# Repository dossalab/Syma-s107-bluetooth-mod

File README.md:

## Syma S107 Bluetooth mod

Syma S107 is a toy helicopter model being popular in early-2010s. It's rather well known because of its low cost, good flying characteristics and sturdy body resistant to crashes.

The original remote control system uses infrared communication - similar to how classic TV remotes work. The major drawback of such solution is that it's very sensitive to direct sunlight - making it very hard (and even slightly dangerous) to fly this toy outside. This also requires keeping a dedicated remote which is larger than this toy and always tend to go missing :)

This is a complete redesign of original motherboard, featuring Bluetooth LE with broader range and smartphone compatibility, battery charger with USB port and battery level reporting, additional outputs and custom, hackable firmware!

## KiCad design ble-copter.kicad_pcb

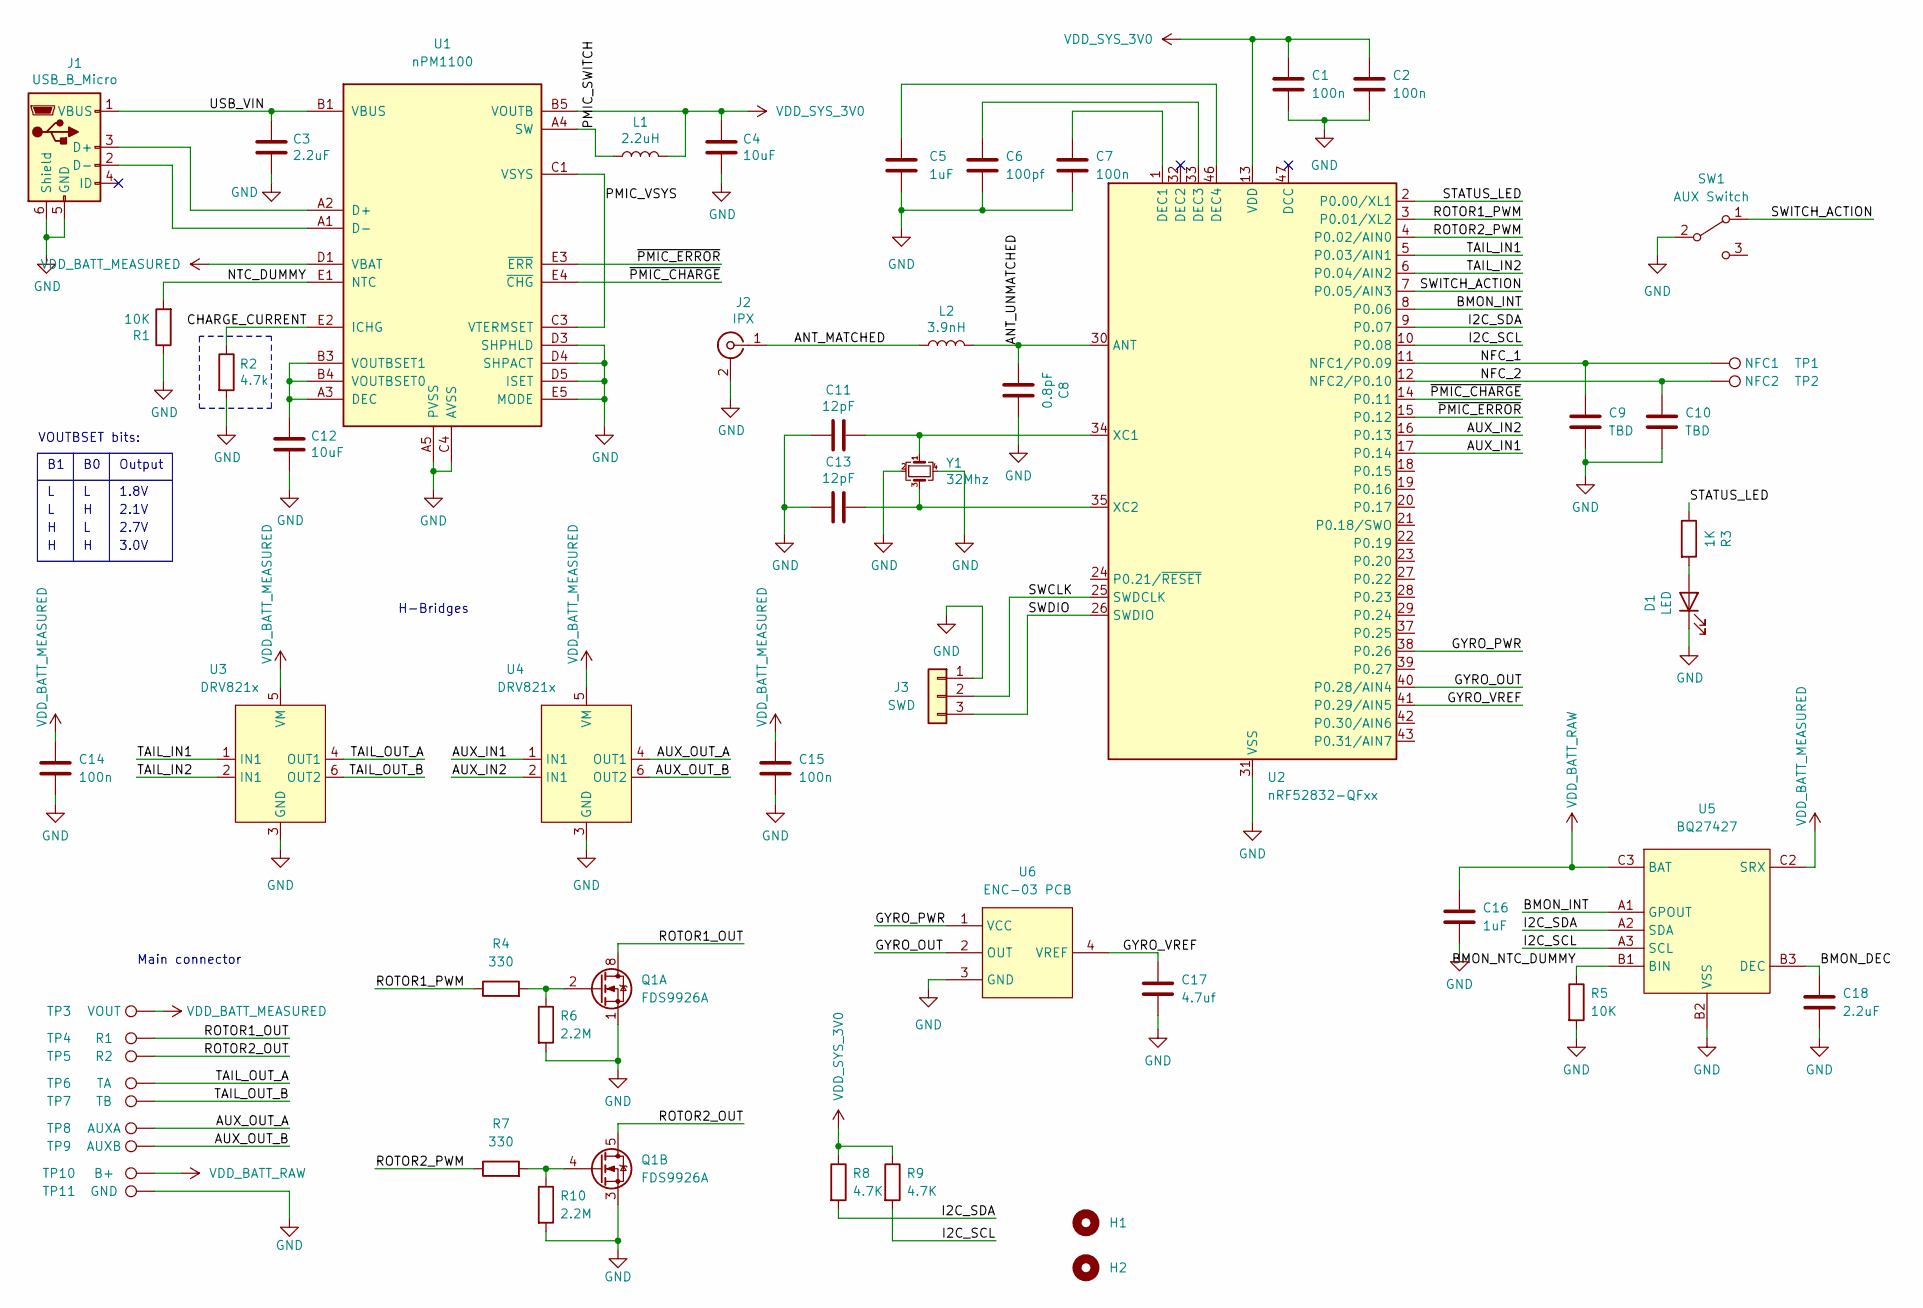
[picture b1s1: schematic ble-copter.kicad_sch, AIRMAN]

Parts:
C1, C2, C7, C14, C15: 100n; C_0603_1608Metric
C3, C18: 2.2uF; C_0603_1608Metric
C4, C12: 10uF; C_0603_1608Metric
C5, C16: 1uF; C_0603_1608Metric
C6: 100pf; C_0603_1608Metric
C8: 0.8pF; C_0603_1608Metric
C9, C10: TBD; C_0603_1608Metric
C11, C13: 12pF; C_0603_1608Metric
C17: 4.7uf; C_0603_1608Metric
D1: LED; LED_0603_1608Metric
H1, H2: MountingHole; MountingHole_1.6mm
J1: USB_B_Micro; USB_Micro-B_Wuerth_629105150521
J2: IPX; U.FL_Hirose_U.FL-R-SMT-1_Vertical
J3: SWD; PinHeader_1x03_P1.27mm_Vertical
L1: 2.2uH; L_0805_2012Metric
L2: 3.9nH; L_0603_1608Metric
Q1: FDS9926A; SOIC-8_3.9x4.9mm_P1.27mm
R1, R5: 10K; R_0603_1608Metric
R2: 4.7k; R_0603_1608Metric
R3: 1K; R_0603_1608Metric
R4, R7: 330; R_0603_1608Metric
R6, R10: 2.2M; R_0603_1608Metric
R8, R9: 4.7K; R_0603_1608Metric
SW1: AUX Switch; SW_SPDT_PCM12
TP1: NFC1; TestPoint_THTPad_D1.0mm_Drill0.5mm
TP2: NFC2; TestPoint_THTPad_D1.0mm_Drill0.5mm
TP3: VOUT; TestPoint_THTPad_D1.0mm_Drill0.5mm
TP4: R1; TestPoint_THTPad_D1.0mm_Drill0.5mm
TP5: R2; TestPoint_THTPad_D1.0mm_Drill0.5mm
TP6: TA; TestPoint_THTPad_D1.0mm_Drill0.5mm
TP7: TB; TestPoint_THTPad_D1.0mm_Drill0.5mm
TP8: AUXA; TestPoint_THTPad_D1.0mm_Drill0.5mm
TP9: AUXB; TestPoint_THTPad_D1.0mm_Drill0.5mm
TP10: B+; TestPoint_THTPad_D1.0mm_Drill0.5mm
TP11: GND; TestPoint_THTPad_D1.0mm_Drill0.5mm
U1: nPM1100; Nordic_WLCSP-25_5x5_2.075x2.075mm
U2: nRF52832-QFxx; QFN-48-1EP_6x6mm_P0.4mm_EP4.6x4.6mm
U3, U4: DRV821x; SOT-563
U5: BQ27427; BGA-9_3x3_1.6x1.6mm
U6: ENC-03 PCB
Y1: 32Mhz; Crystal_SMD_2520-4Pin_2.5x2.0mm

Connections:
/ANT_MATCHED: J2.1 (In), L2.1
/ANT_UNMATCHED: C8.2, L2.2, U2.30 (ANT)
/AUX_IN1: U2.17 (P0.14), U4.1 (IN1)
/AUX_IN2: U2.16 (P0.13), U4.2 (IN1)
/AUX_OUT_A: TP8.1, U4.4 (OUT1)
/AUX_OUT_B: TP9.1, U4.6 (OUT2)
/BMON_DEC: C18.1, U5.B3 (DEC)
/BMON_INT: U2.8 (P0.06), U5.A1 (GPOUT)
/BMON_NTC_DUMMY: R5.1, U5.B1 (BIN)
/CHARGE_CURRENT: R2.1, U1.E2 (ICHG)
/GYRO_OUT: U2.40 (P0.28/AIN4), U6.2 (OUT)
/GYRO_PWR: U2.38 (P0.26), U6.1 (VCC)
/GYRO_VREF: C17.1, U2.41 (P0.29/AIN5), U6.4 (VREF)
/I2C_SCL: R9.2, U2.10 (P0.08), U5.A3 (SCL)
/I2C_SDA: R8.2, U2.9 (P0.07), U5.A2 (SDA)
/NFC_1: C9.1, TP1.1, U2.11 (NFC1/P0.09)
/NFC_2: C10.1, TP2.1, U2.12 (NFC2/P0.10)
/NTC_DUMMY: R1.2, U1.E1 (NTC)
/PMIC_SWITCH: L1.1, U1.A4 (SW)
/PMIC_VSYS: U1.C1 (VSYS), U1.C2 (VSYS), U1.C3 (VTERMSET)
/ROTOR1_OUT: Q1.7 (D1), Q1.8 (D1), TP4.1
/ROTOR1_PWM: R4.1, U2.3 (P0.01/XL2)
/ROTOR2_OUT: Q1.5 (D2), Q1.6 (D2), TP5.1
/ROTOR2_PWM: R7.1, U2.4 (P0.02/AIN0)
/STATUS_LED: R3.1, U2.2 (P0.00/XL1)
/SWCLK: J3.2, U2.25 (SWDCLK)
/SWDIO: J3.3, U2.26 (SWDIO)
/SWITCH_ACTION: SW1.1 (A), U2.7 (P0.05/AIN3)
/TAIL_IN1: U2.5 (P0.03/AIN1), U3.1 (IN1)
/TAIL_IN2: U2.6 (P0.04/AIN2), U3.2 (IN1)
/TAIL_OUT_A: TP6.1, U3.4 (OUT1)
/TAIL_OUT_B: TP7.1, U3.6 (OUT2)
/~PMIC_CHARGE: U1.E4 (~CHG), U2.14 (P0.11)
/~PMIC_ERROR: U1.E3 (~ERR), U2.15 (P0.12)
GND: C1.2, C2.2, C3.2, C4.2, C5.2, C6.2, C7.2, C8.1, C9.2, C10.2, C11.2, C12.2, C13.2, C14.2, C15.2, C16.2, C17.2, C18.2, D1.1 (K), J1.5 (GND), J1.6 (Shield), J2.2 (Ext), J3.1, Q1.1 (S1), Q1.3 (S2), R1.1, R2.2, R5.2, R6.2, R10.2, SW1.2 (B), TP11.1, U1.A5 (PVSS), U1.C4 (AVSS), U1.C5 (AVSS), U1.D3 (SHPHLD), U1.D4 (SHPACT), U1.D5 (ISET), U1.E5 (MODE), U2.31 (VSS), U2.45 (VSS), U2.49 (VSS), U3.3 (GND), U4.3 (GND), U5.B2 (VSS), U5.C1 (VSS), U6.3 (GND), Y1.2, Y1.4
unnamed: C5.1, U2.46 (DEC4)
unnamed: C6.1, U2.33 (DEC3)
unnamed: C7.1, U2.1 (DEC1)
unnamed: C11.1, U2.34 (XC1), Y1.1
unnamed: C12.1, U1.A3 (DEC), U1.B3 (VOUTBSET1), U1.B4 (VOUTBSET0)
unnamed: C13.1, U2.35 (XC2), Y1.3
unnamed: D1.2 (A), R3.2
unnamed: J1.2 (D-), U1.A1 (D-)
unnamed: J1.3 (D+), U1.A2 (D+)
unnamed: Q1.2 (G1), R4.2, R6.1
unnamed: Q1.4 (G2), R7.2, R10.1
VBAT: C14.1, C15.1, TP3.1, U1.D1 (VBAT), U1.D2 (VBAT), U3.5 (VM), U4.5 (VM), U5.C2 (SRX)
VBUS: C3.1, J1.1 (VBUS), U1.B1 (VBUS), U1.B2 (VBUS)
VDD_BATT_RAW: C16.1, TP10.1, U5.C3 (BAT)
VDD_SYS_3V0: C1.1, C2.1, C4.1, L1.2, R8.1, R9.1, U1.B5 (VOUTB), U2.13 (VDD), U2.36 (VDD), U2.48 (VDD)

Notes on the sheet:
Output
2.1V
VOUTBSET bits:
Main connector
H-Bridges
2.7V
3.0V
1.8V

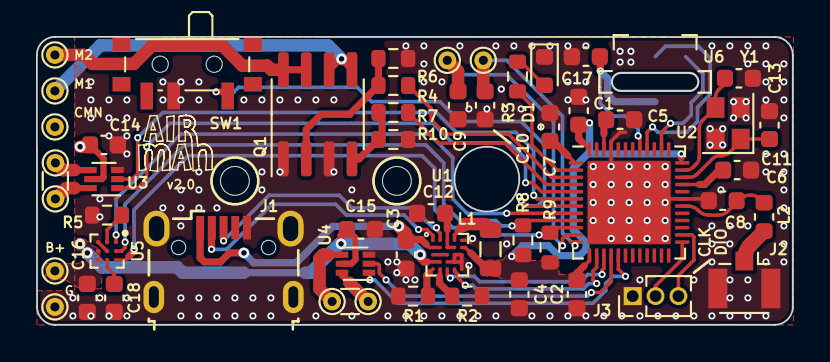
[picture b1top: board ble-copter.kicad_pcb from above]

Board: 2 copper layers, 42.0 x 16.0 mm, 56 parts (0 on the bottom side), 50 nets.

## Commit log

2023-02-13 init commit
2023-02-13 add README.md
2023-02-13 add schematics as a pdf
2025-10-05 Kicad 9.0
2025-10-05 move pcb to a separate directory
2025-10-05 firmware init commit
2025-10-05 more power related work
2025-10-05 slow down blinking a bit
2025-10-05 control task
2025-10-05 basic charge monitoring
2025-10-05 add basic controller
2025-10-05 bring fuelgauge driver
2025-10-05 move firmware to a separate directory
2025-10-05 bump readme
2025-10-11 sync with the latest embassy
2025-10-11 add mwu high current consumption workaround
2025-10-11 update the sine sequence
2025-10-23 make sure controller drops PWM on disconnection
2025-10-25 do not use PWM sequencer for indications
    power saving - use simple timer blinky
2025-10-25 add peripheral role to ble
    allow connection from a phone or computer to dump debug information,
    configure settings and so on
2025-10-25 unite fuelgauge and charger resources
2025-10-25 set I2C interrupt priority
2025-10-25 change project name
2025-10-25 use shared i2c bus
2025-10-26 move ble stuff to a separate mod
2025-11-05 increase base frequency for PWM
    less audible noise, smoother operation
2025-11-05 fix the pwm-inverted issue
    upstream embassy fixed the inverted pwm! so we can now switch away from
    the fork
2025-11-05 print fuelgauge initialization error
2025-11-05 system message bus
2025-11-05 new gauge memory interface + ble stats
2025-11-08 revisit the power system
2025-11-20 set PWM divider to 16
    divider 1 does not work well for tail's motor H-Bridge. TI!
2025-11-23 more improvements to fuelgauge sensing
2025-11-23 don't store last periodic update
    updates are instant measurements so no need to have the last value stored
2025-11-23 advertise the power service to help with scanning
2025-11-23 get some gyroscope data
2025-11-30 better controller + pid
2025-11-30 rename powerstats -> systemstate
2025-12-07 change loglevel
    we seem to be running out of memory, so let's avoid
    adding low-level debug info to the binary
2025-12-07 run_while helper to run stuff while we're in a specific state
2025-12-20 remove bleeventsproxy, use our shared state instead
2026-01-18 use defmt::unwrap instead of .unwrap
2026-01-31 more agressive pids
2026-01-31 rework system state
2026-02-01 indications rework
2026-02-01 host requests support for fuelgauge reset and firmware restart
2026-02-01 make sure CC gain is set correctly after user-induced reset
2026-02-01 simplify and debug indications
2026-02-03 better fuel gauge manager
2026-05-08 power state machine fixes (claude)
2026-05-08 ble fixes (claude)
2026-05-08 start scan on demand (claude)
2026-05-08 set initial timestamps value
2026-05-21 switch to code generation for gatt, switch to floats for PID
2026-05-21 controller connection state + scanner state + ratable + small notification rework
2026-05-21 expo for yaw
2026-05-23 combine expo settings with pid settings under a new configuration service
2026-05-24 better security handling for central
2026-05-24 bump embassy + softdevice, long char read support
